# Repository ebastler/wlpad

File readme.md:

# wlpad
wlpad is a simple wireless numpad, designed around a moko MK08A module, and fitting both Hi-Tek 725 as well as MX switches. While the PCB is the same for both switch types, the plate is different.

### Features
* Runs ZMK firmware on a Moko MK08A module - firmware can be found in my [zmk-config](https://github.com/ebastler/zmk-config) repo
* Hi-Tek 725 and Cherry MX compatibility
* Molex Picoblade connectors for battery and plate connection
* Charge indicator LED, some WS2812_2020 and a small 128x32px OLED can be placed on the plate

This PCB was painly made as a proof-of-concept for my Hi-Tek 725 footprints, and to try the MK08A module and MAX17048 fuel gauge chip on an actual PCB. The latter already found its way into my [Osprey](https://github.com/ebastler/osprey). 

rc1.0 had some issues (vertical 2u keys rotated by 180°, LEDs on plate connected to GND instead of VDD), which were addressed by the current rc1.1 version. However, the rc1.1 version has not been (and probably will not be) prototyped - use at your own risk. Please report back if you successfully tested such a PCB.

### Renders (rc1.1)

### Pixtures (rc1.0)

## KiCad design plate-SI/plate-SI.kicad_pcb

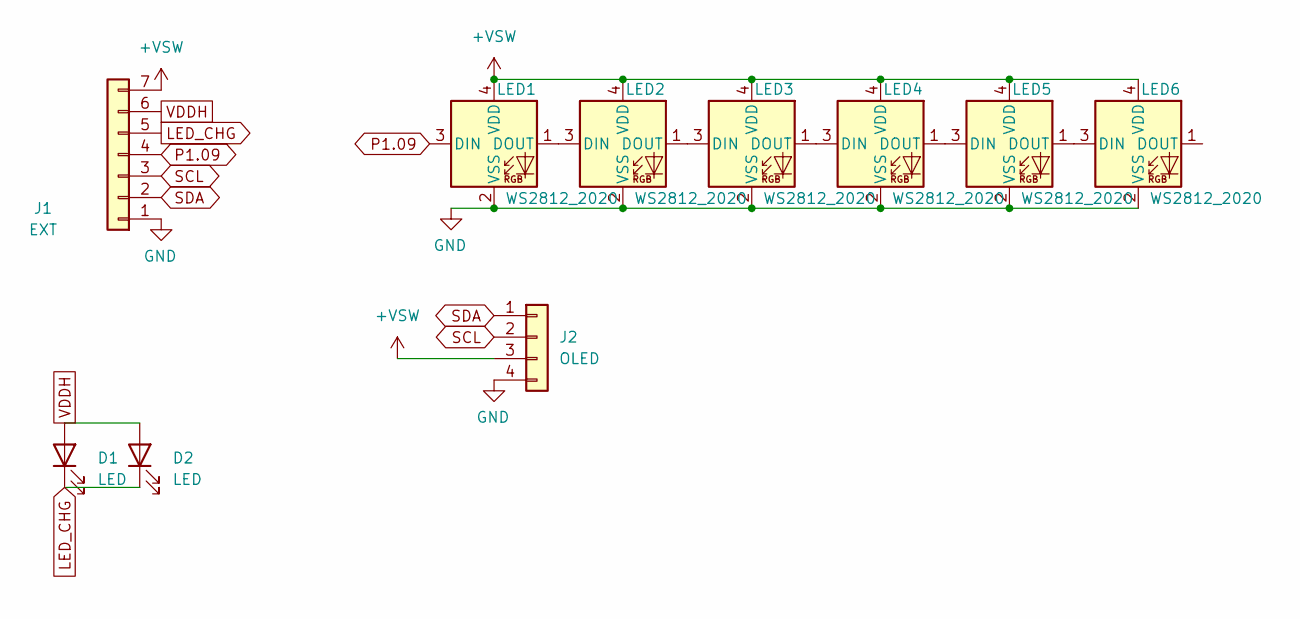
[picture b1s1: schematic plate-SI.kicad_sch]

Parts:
D1: LED; LED_0805_2012Metric_Pad1.15x1.40mm_HandSolder
D2: LED; LED_Rectangular_W3.0mm_H2.0mm
J1: EXT; Molex_PicoBlade_53048-0710_1x07_P1.25mm_Horizontal
J2: OLED; PinHeader_1x04_P2.54mm_Vertical
LED1, LED2, LED3, LED4, LED5, LED6: WS2812_2020; LED_WS2812_2020

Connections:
+VSW: J1.7, J2.3, LED1.4 (VDD), LED2.4 (VDD), LED3.4 (VDD), LED4.4 (VDD), LED5.4 (VDD), LED6.4 (VDD)
GND: J1.1, J2.4, LED1.2 (VSS), LED2.2 (VSS), LED3.2 (VSS), LED4.2 (VSS), LED5.2 (VSS), LED6.2 (VSS)
LED_CHG: D1.1 (K), D2.1 (K), J1.5
unnamed: LED1.1 (DOUT), LED2.3 (DIN)
unnamed: LED2.1 (DOUT), LED3.3 (DIN)
unnamed: LED3.1 (DOUT), LED4.3 (DIN)
unnamed: LED4.1 (DOUT), LED5.3 (DIN)
unnamed: LED5.1 (DOUT), LED6.3 (DIN)
P1.09: J1.4, LED1.3 (DIN)
SCL: J1.3, J2.2
SDA: J1.2, J2.1
VDDH: D1.2 (A), D2.2 (A), J1.6

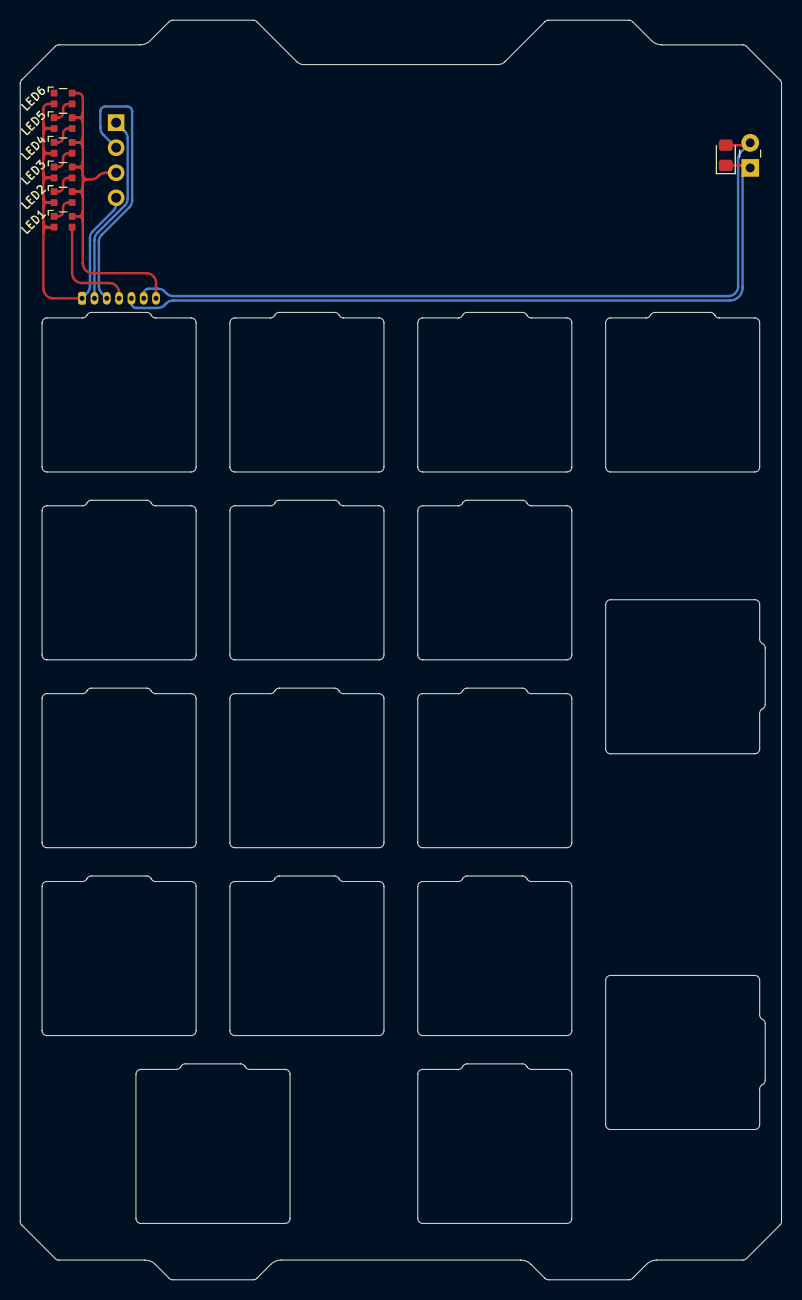
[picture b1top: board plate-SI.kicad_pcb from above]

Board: 2 copper layers, 77.2 x 127.7 mm, 10 parts (1 on the bottom side), 12 nets.

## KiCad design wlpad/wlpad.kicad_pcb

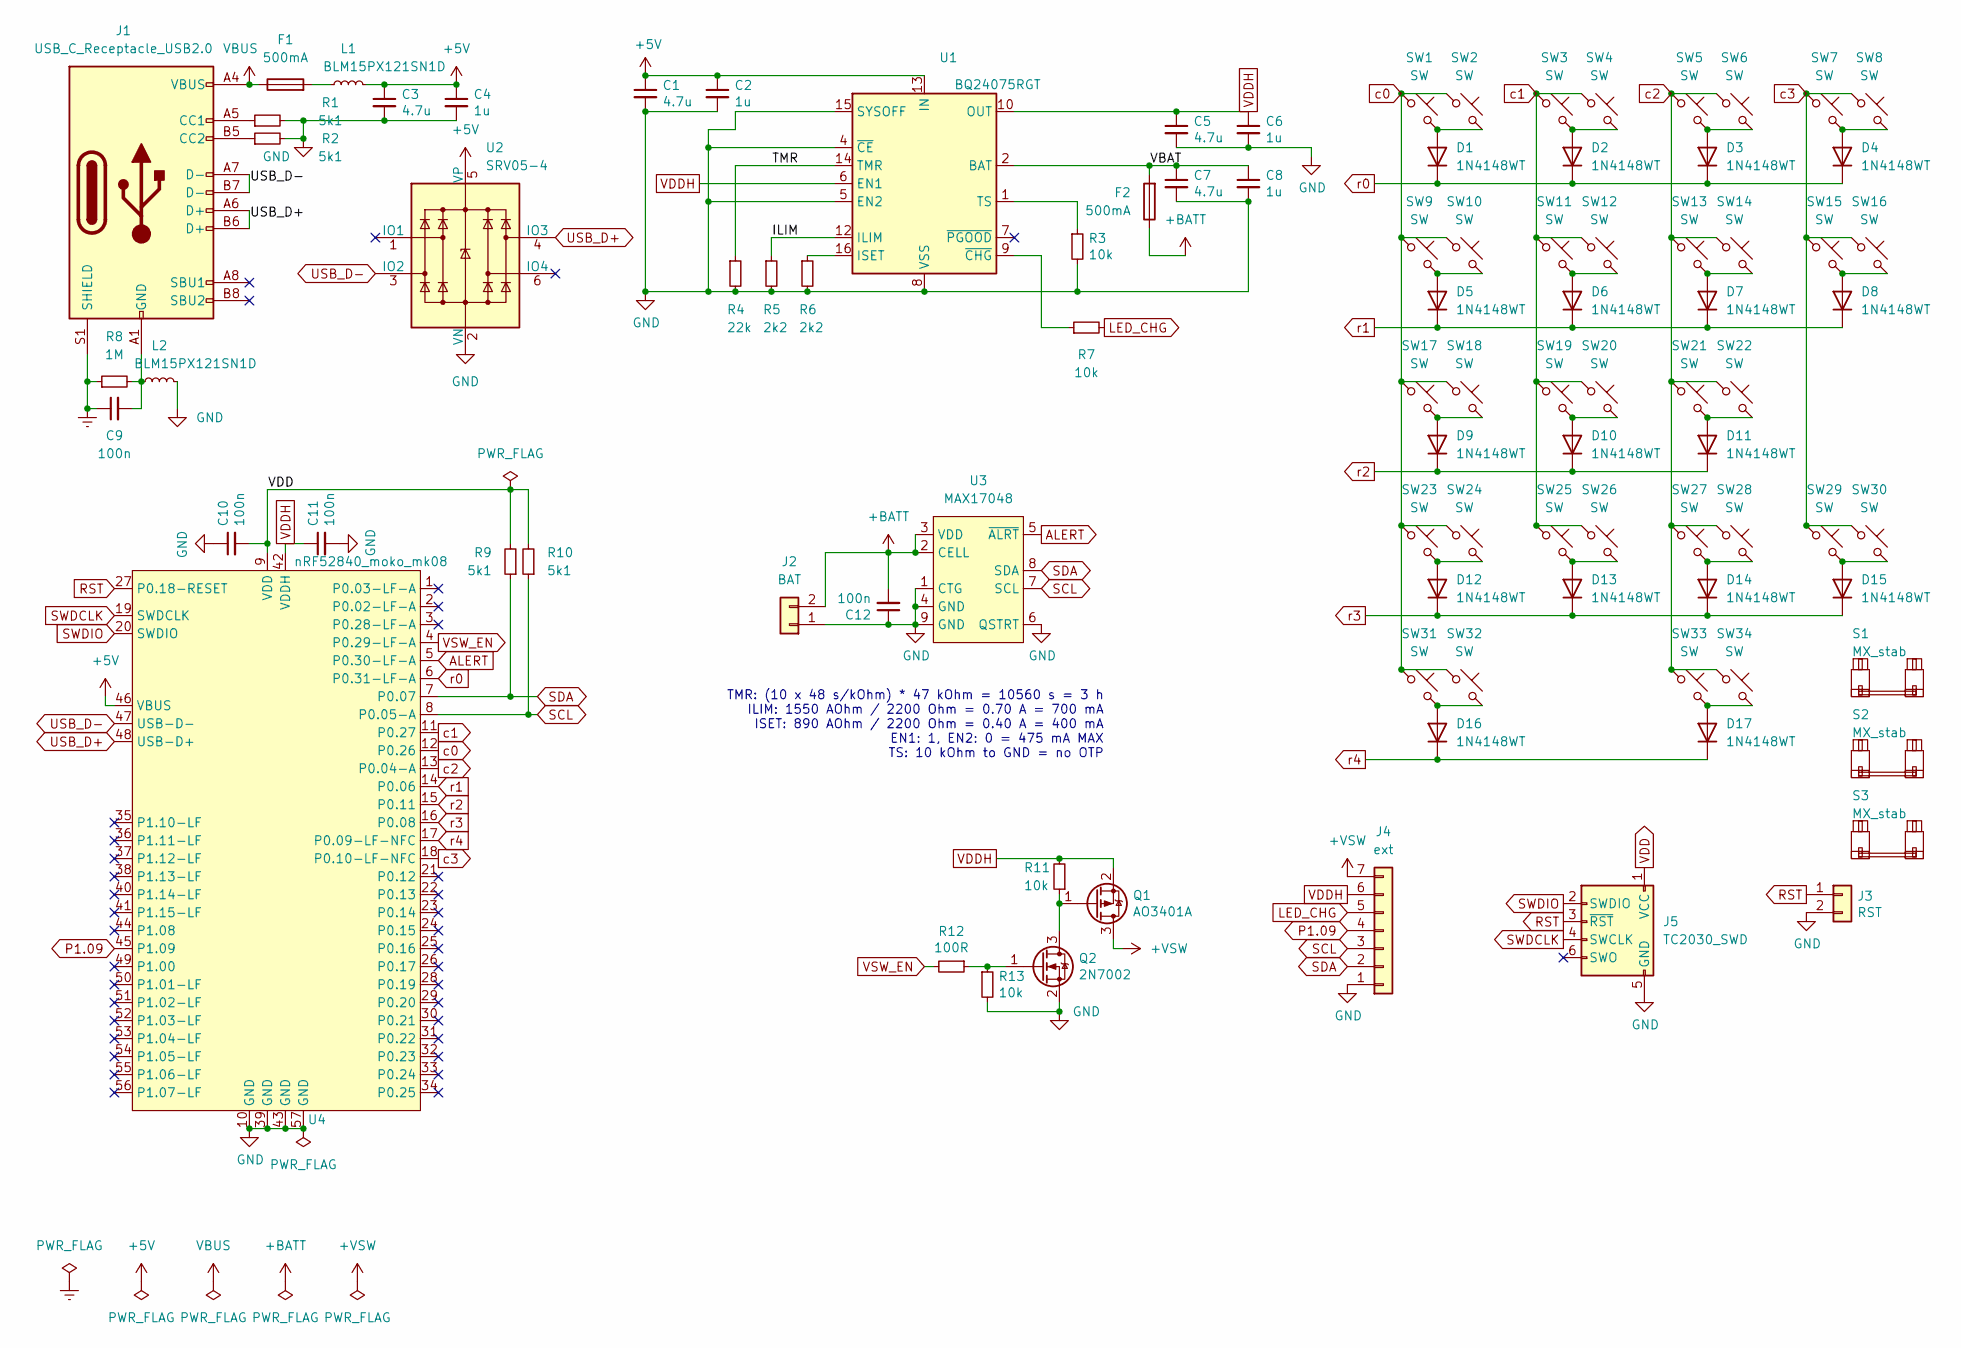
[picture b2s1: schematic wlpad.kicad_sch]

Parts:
C1, C3, C5, C7: 4.7u; C_0402_1005Metric; LCSC C23733
C2, C4, C6, C8: 1u; C_0402_1005Metric; LCSC C52923
C9: 100n; C_0402_1005Metric
C10, C11, C12: 100n; C_0402_1005Metric; LCSC C52923
D1, D2, D3, D4, D5, D6, D7, D8, D9, D10, D11, D12, D13, D14, D15, D16, D17: 1N4148WT; D_SOD-523
F1, F2: 500mA; Fuse_0603_1608Metric
J1: USB_C_Receptacle_USB2.0; USB_C_Receptacle_HRO_TYPE-C-31-M-12
J2: BAT; Molex_PicoBlade_53048-0210_1x02_P1.25mm_Horizontal
J3: RST; PinHeader_1x02_P2.54mm_Vertical
J4: ext; Molex_PicoBlade_53048-0710_1x07_P1.25mm_Horizontal
J5: TC2030_SWD; CON_TC2030_outlined
L1, L2: BLM15PX121SN1D; L_0402_1005Metric; LCSC C88970
Q1: AO3401A; SOT-23
Q2: 2N7002; SOT-23
R1, R2, R9, R10: 5k1; R_0402_1005Metric
R3, R7: 10k; R_0402_1005Metric; LCSC C25744
R4: 22k; R_0402_1005Metric; LCSC C25792
R5: 2k2; R_0402_1005Metric; LCSC C25867
R6: 2k2; R_0402_1005Metric; LCSC C25744
R8: 1M; R_0402_1005Metric
R11, R13: 10k; R_0402_1005Metric
R12: 100R; R_0402_1005Metric
S1, S2, S3: MX_stab; STAB_MX_P_2u
SW1, SW3, SW5, SW7, SW9, SW11, SW13, SW15, SW17, SW19, SW21, SW23, SW25, SW27, SW29, SW31, SW33: SW; SW_HiTek_1u
SW2, SW4, SW6, SW8, SW10, SW12, SW14, SW16, SW18, SW20, SW22, SW24, SW26, SW28, SW30, SW32, SW34: SW; SW_MX_1u
U1: BQ24075RGT; VQFN-16-1EP_3x3mm_P0.5mm_EP1.6x1.6mm
U2: SRV05-4; SOT-23-6
U3: MAX17048; DFN-8-1EP_2x2mm_P0.5mm_EP0.7x1.3mm
U4: nRF52840_moko_mk08; nRF52840_moko_mk08_HS

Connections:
+5V: C1.1, C2.1, C3.1, C4.1, L1.2, U1.13 (IN), U2.5 (VP), U4.46 (VBUS)
+BATT: C12.2, F2.1, J2.2, U3.2 (CELL), U3.3 (VDD)
+VSW: J4.7, Q1.3 (D)
/ILIM: R5.1, U1.12 (ILIM)
/TMR: R4.1, U1.14 (TMR)
/VBAT: C7.1, C8.1, F2.2, U1.2 (BAT), U1.3 (BAT)
ALERT: U3.5 (~ALRT), U4.5 (P0.30-LF-A)
Earth: C9.1, J1.S1 (SHIELD), R8.1
GND: C1.2, C2.2, C3.2, C4.2, C5.2, C6.2, C7.2, C8.2, C10.1, C11.2, C12.1, J2.1, J3.2, J4.1, J5.5 (GND), L2.2, Q2.2 (S), R1.2, R2.2, R3.2, R4.2, R5.2, R6.2, R13.2, U1.4 (~CE), U1.5 (EN2), U1.8 (VSS), U1.15 (SYSOFF), U1.17 (VSS), U2.2 (VN), U3.1 (CTG), U3.4 (GND), U3.6 (QSTRT), U3.9 (GND), U4.10 (GND), U4.39 (GND), U4.43 (GND), U4.57 (GND)
LED_CHG: J4.5, R7.2
unnamed: C9.2, J1.A1 (GND), J1.A12 (GND), J1.B1 (GND), J1.B12 (GND), L2.1, R8.2
unnamed: D1.2 (A), SW1.2, SW2.2
unnamed: D2.2 (A), SW3.2, SW4.2
unnamed: D3.2 (A), SW5.2, SW6.2
unnamed: D4.2 (A), SW7.2, SW8.2
unnamed: D5.2 (A), SW9.2, SW10.2
unnamed: D6.2 (A), SW11.2, SW12.2
unnamed: D7.2 (A), SW13.2, SW14.2
unnamed: D8.2 (A), SW15.2, SW16.2
unnamed: D9.2 (A), SW17.2, SW18.2
unnamed: D10.2 (A), SW19.2, SW20.2
unnamed: D11.2 (A), SW21.2, SW22.2
unnamed: D12.2 (A), SW23.2, SW24.2
unnamed: D13.2 (A), SW25.2, SW26.2
unnamed: D14.2 (A), SW27.2, SW28.2
unnamed: D15.2 (A), SW29.2, SW30.2
unnamed: D16.2 (A), SW31.2, SW32.2
unnamed: D17.2 (A), SW33.2, SW34.2
unnamed: F1.2, L1.1
unnamed: J1.A5 (CC1), R1.1
unnamed: J1.B5 (CC2), R2.1
unnamed: Q1.1 (G), Q2.3 (D), R11.1
unnamed: Q2.1 (G), R12.1, R13.1
unnamed: R6.1, U1.16 (ISET)
unnamed: R3.1, U1.1 (TS)
unnamed: R7.1, U1.9 (~CHG)
P1.09: J4.4, U4.45 (P1.09)
RST: J3.1, J5.3 (~RST), U4.27 (P0.18-RESET)
SCL: J4.3, R10.1, U3.7 (SCL), U4.8 (P0.05-A)
SDA: J4.2, R9.1, U3.8 (SDA), U4.7 (P0.07)
SWDCLK: J5.4 (SWCLK), U4.19 (SWDCLK)
SWDIO: J5.2 (SWDIO), U4.20 (SWDIO)
USB_D+: J1.A6 (D+), J1.B6 (D+), U2.4 (IO3), U4.48 (USB-D+)
USB_D-: J1.A7 (D-), J1.B7 (D-), U2.3 (IO2), U4.47 (USB-D-)
VBUS: F1.1, J1.A4 (VBUS), J1.A9 (VBUS), J1.B4 (VBUS), J1.B9 (VBUS)
VDD: C10.2, J5.1 (VCC), R9.2, R10.2, U4.9 (VDD)
VDDH: C5.1, C6.1, C11.1, J4.6, Q1.2 (S), R11.2, U1.6 (EN1), U1.10 (OUT), U1.11 (OUT), U4.42 (VDDH)
VSW_EN: R12.2, U4.4 (P0.29-LF-A)
c0: SW1.1, SW2.1, SW9.1, SW10.1, SW17.1, SW18.1, SW23.1, SW24.1, SW31.1, SW32.1, U4.12 (P0.26)
c1: SW3.1, SW4.1, SW11.1, SW12.1, SW19.1, SW20.1, SW25.1, SW26.1, U4.11 (P0.27)
c2: SW5.1, SW6.1, SW13.1, SW14.1, SW21.1, SW22.1, SW27.1, SW28.1, SW33.1, SW34.1, U4.13 (P0.04-A)
c3: SW7.1, SW8.1, SW15.1, SW16.1, SW29.1, SW30.1, U4.18 (P0.10-LF-NFC)
r0: D1.1 (K), D2.1 (K), D3.1 (K), D4.1 (K), U4.6 (P0.31-LF-A)
r1: D5.1 (K), D6.1 (K), D7.1 (K), D8.1 (K), U4.14 (P0.06)
r2: D9.1 (K), D10.1 (K), D11.1 (K), U4.15 (P0.11)
r3: D12.1 (K), D13.1 (K), D14.1 (K), D15.1 (K), U4.16 (P0.08)
r4: D16.1 (K), D17.1 (K), U4.17 (P0.09-LF-NFC)

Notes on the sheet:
TMR: (10 x 48 s/kOhm) * 47 kOhm = 10560 s = 3 h ILIM: 1550 AOhm / 2200 Ohm = 0.70 A = 700 mA ISET: 890 AOhm / 2200 Ohm = 0.40 A = 400 mA EN1: 1, EN2: 0 = 475 mA MAX TS: 10 kOhm to GND = no OTP

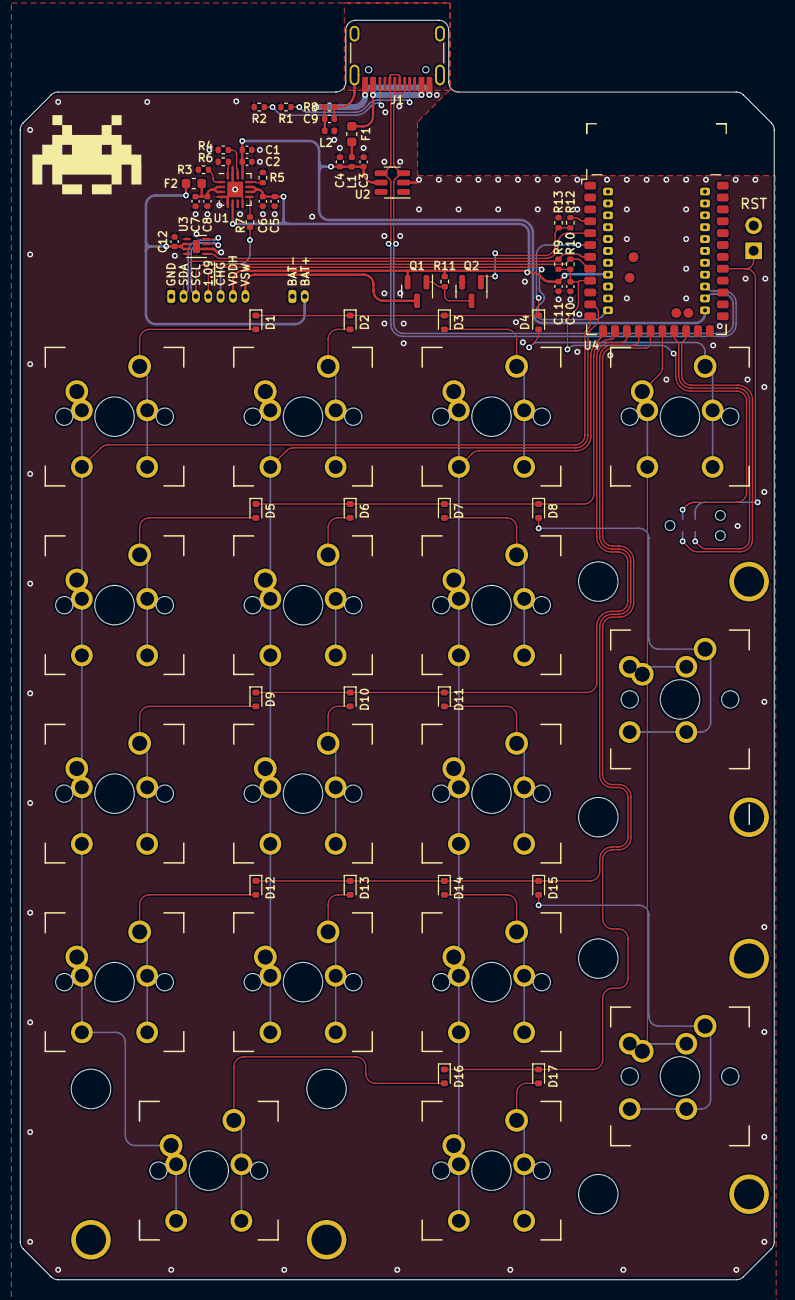
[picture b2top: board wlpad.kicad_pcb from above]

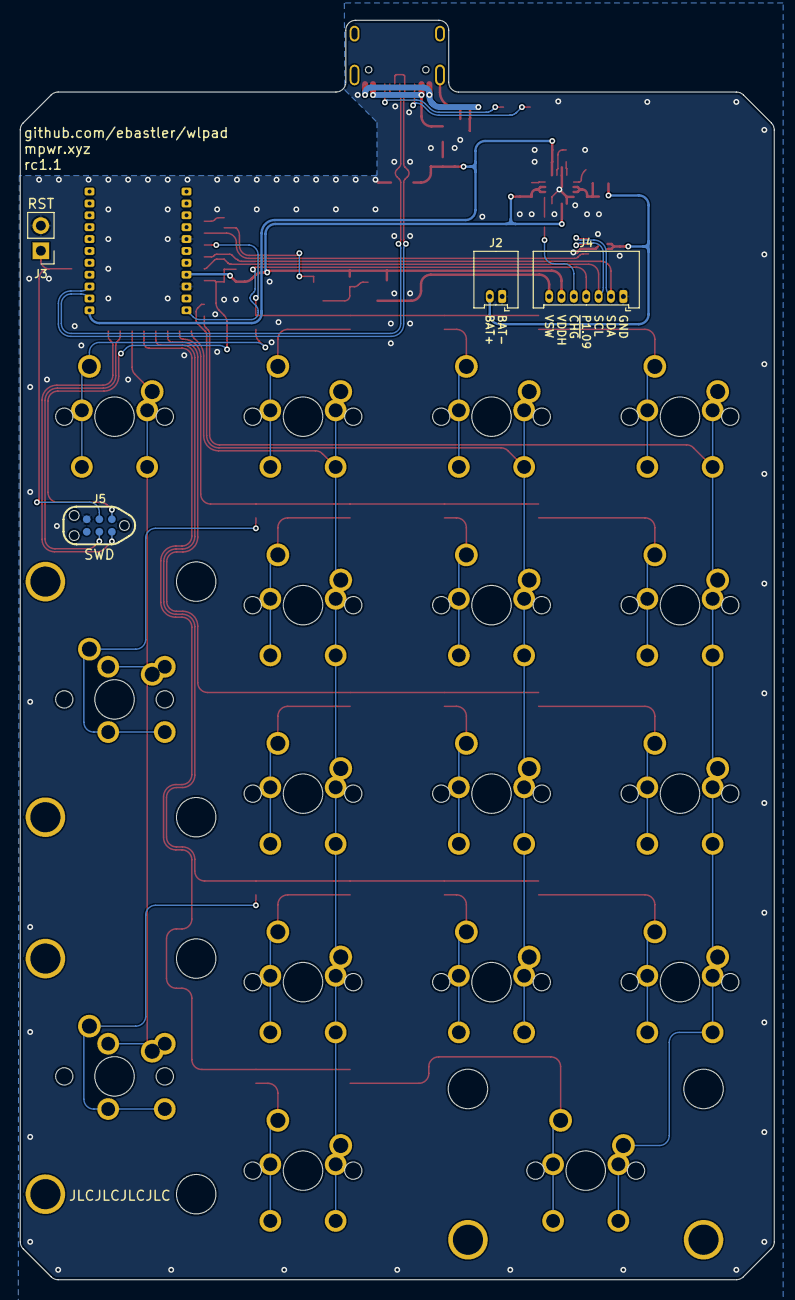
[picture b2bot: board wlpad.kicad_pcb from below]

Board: 2 copper layers, 76.2 x 127.3 mm, 94 parts (4 on the bottom side), 57 nets.

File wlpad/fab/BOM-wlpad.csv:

Comment,Designator,Footprint,LCSC
AO3401A,Q1,SOT-23,C15127
USB_C_Receptacle_USB2.0,J1,USB_C_Receptacle_HRO_TYPE-C-31-M-12,C165948
500mA,"F1,F2",Fuse_0603_1608Metric,C210357
4.7u,"C1,C3,C5,C7",C_0402_1005Metric,C23733
100R,R12,R_0402_1005Metric,C25076
10k,"R11,R13,R3,R6,R7",R_0402_1005Metric,C25744
22k,R4,R_0402_1005Metric,C25792
2k2,R5,R_0402_1005Metric,C25867
5k1,"R1,R10,R2,R9",R_0402_1005Metric,C25905
1M,R8,R_0402_1005Metric,C26083
MAX17048,U3,DFN-8-1EP_2x2mm_P0.5mm_EP0.7x1.3mm,C2682616
BQ24075RGT,U1,VQFN-16-1EP_3x3mm_P0.5mm_EP1.6x1.6mm,C2865459
1N4148WT,"D1,D10,D11,D12,D13,D14,D15,D16,D17,D2,D3,D4,D5,D6,D7,D8,D9",D_SOD-523,C511874
100n,"C10,C11,C12,C2,C4,C6,C8,C9",C_0402_1005Metric,C52923
SRV05-4,U2,SOT-23-6,C558418
2N7002,Q2,SOT-23,C8545
BLM15PX121SN1D,"L1,L2",L_0402_1005Metric,C88970
ext,J4,Molex_PicoBlade_53048-0710_1x07_P1.25mm_Horizontal,
BAT,J2,Molex_PicoBlade_53048-0210_1x02_P1.25mm_Horizontal,

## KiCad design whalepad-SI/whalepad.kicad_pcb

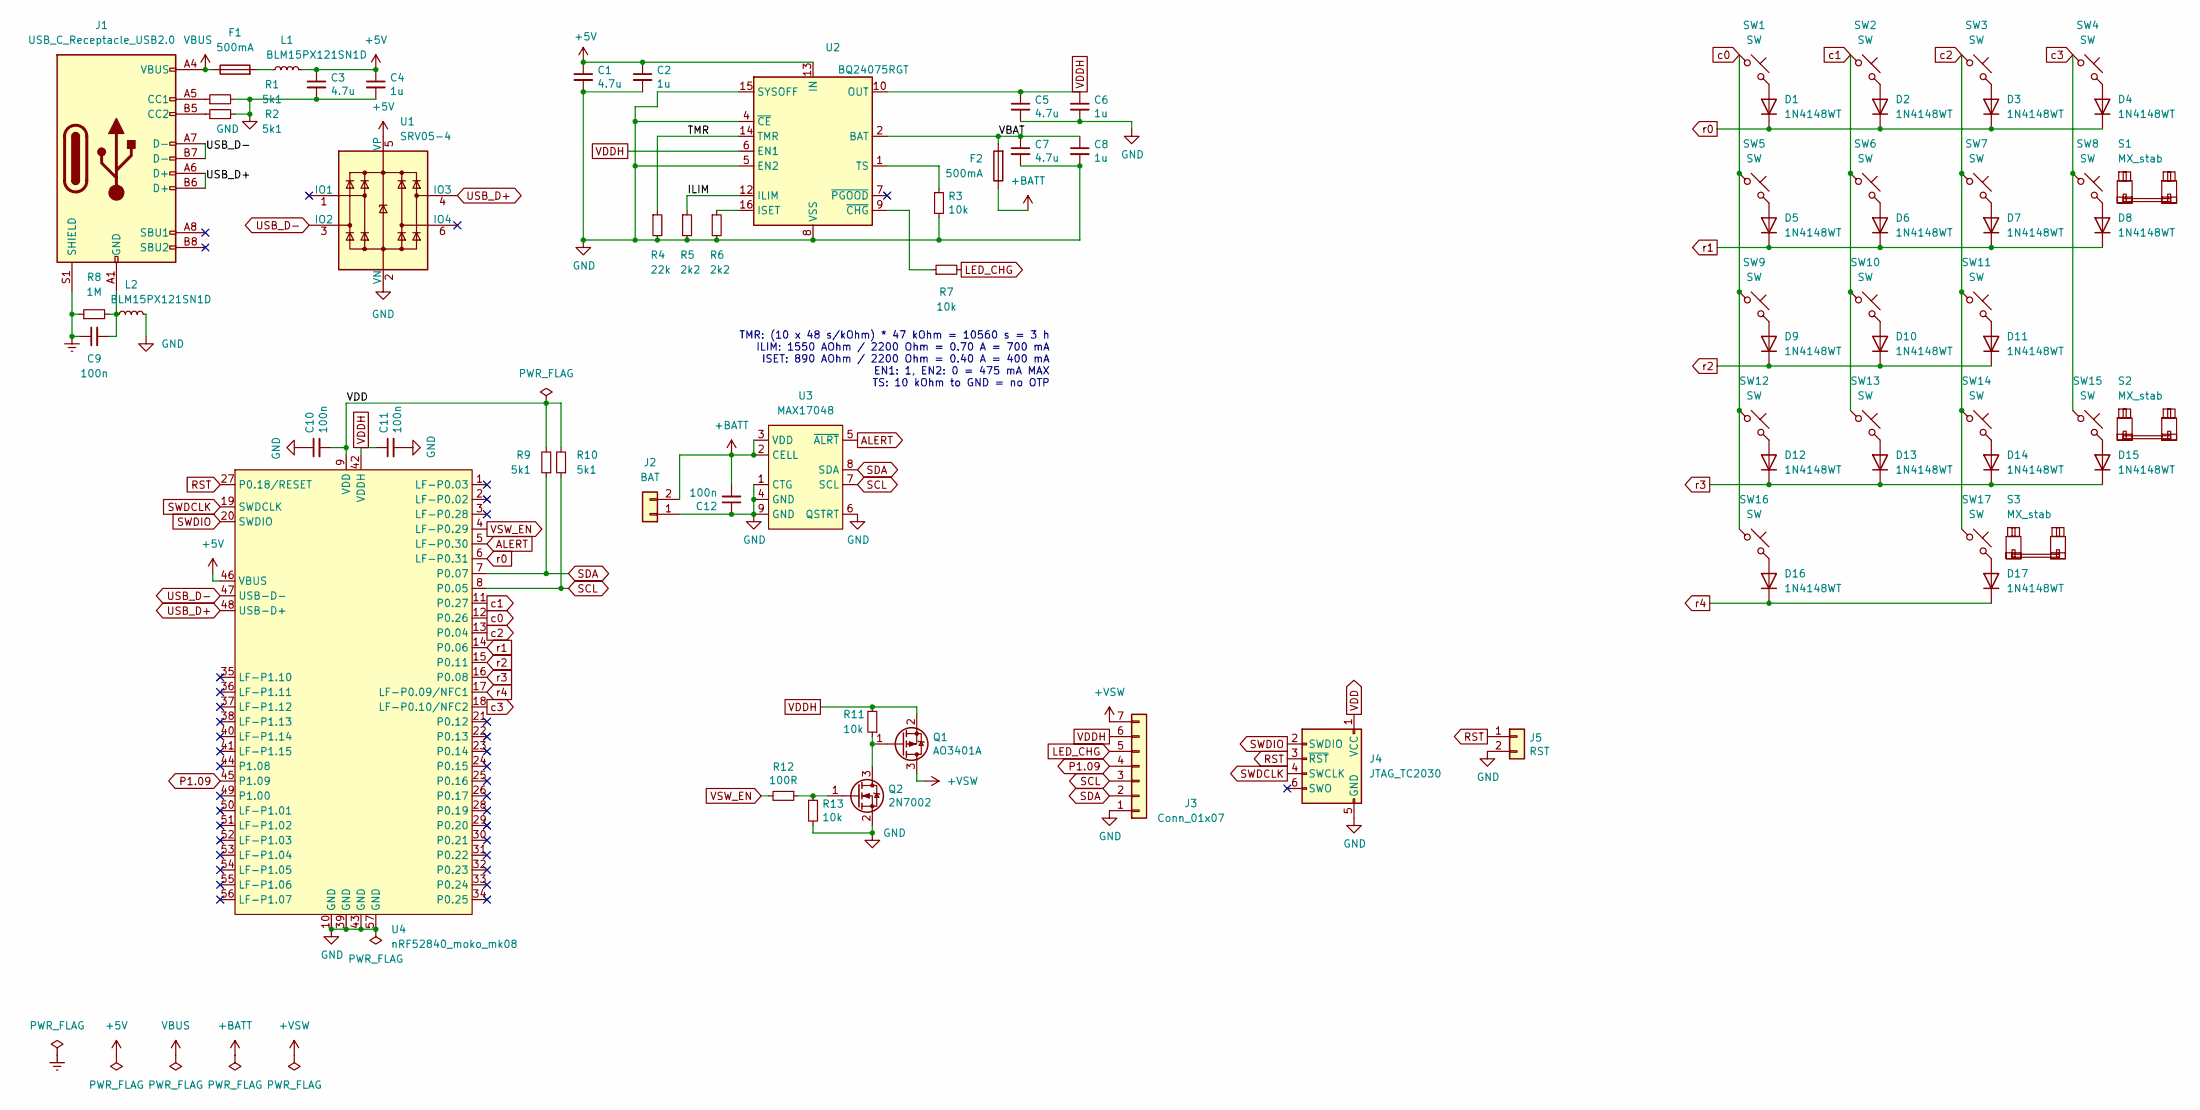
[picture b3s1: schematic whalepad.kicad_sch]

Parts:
C1, C3, C5, C7: 4.7u; C_0402_1005Metric; LCSC C23733
C2, C4, C6, C8: 1u; C_0402_1005Metric; LCSC C52923
C9: 100n; C_0402_1005Metric
C10, C11, C12: 100n; C_0402_1005Metric; LCSC C52923
D1, D2, D3, D4, D5, D6, D7, D8, D9, D10, D11, D12, D13, D14, D15, D16, D17: 1N4148WT; D_SOD-523
F1, F2: 500mA; Fuse_0603_1608Metric
J1: USB_C_Receptacle_USB2.0; USB_C_Receptacle_HRO_TYPE-C-31-M-12
J2: BAT; Molex_PicoBlade_53048-0210_1x02_P1.25mm_Horizontal
J3: Conn_01x07; Molex_PicoBlade_53048-0710_1x07_P1.25mm_Horizontal
J4: JTAG_TC2030; CON_TC2030_outlined
J5: RST; PinHeader_1x02_P2.54mm_Vertical
L1, L2: BLM15PX121SN1D; L_0402_1005Metric; LCSC C88970
Q1: AO3401A; SOT-23
Q2: 2N7002; SOT-23
R1, R2, R9, R10: 5k1; R_0402_1005Metric
R3, R7: 10k; R_0402_1005Metric; LCSC C25744
R4: 22k; R_0402_1005Metric; LCSC C25792
R5: 2k2; R_0402_1005Metric; LCSC C25867
R6: 2k2; R_0402_1005Metric; LCSC C25744
R8: 1M; R_0402_1005Metric
R11, R13: 10k; R_0402_1005Metric
R12: 100R; R_0402_1005Metric
S1, S2, S3: MX_stab; STAB_MX_P_2u
SW1, SW2, SW3, SW4, SW5, SW6, SW7, SW8, SW9, SW10, SW11, SW12, SW13, SW14, SW15, SW16, SW17: SW; SW_HiTek_MX_1u
U1: SRV05-4; SOT-23-6
U2: BQ24075RGT; VQFN-16-1EP_3x3mm_P0.5mm_EP1.6x1.6mm
U3: MAX17048; DFN-8-1EP_2x2mm_P0.5mm_EP0.7x1.3mm
U4: nRF52840_moko_mk08

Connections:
+5V: C1.1, C2.1, C3.1, C4.1, L1.2, U1.5 (VP), U2.13 (IN), U4.46 (VBUS)
+BATT: C12.2, F2.1, J2.2, U3.2 (CELL), U3.3 (VDD)
+VSW: J3.7, Q1.3 (D)
/ILIM: R5.1, U2.12 (ILIM)
/TMR: R4.1, U2.14 (TMR)
/VBAT: C7.1, C8.1, F2.2, U2.2 (BAT), U2.3 (BAT)
ALERT: U3.5 (~ALRT), U4.5 (LF-P0.30)
Earth: C9.1, J1.S1 (SHIELD), R8.1
GND: C1.2, C2.2, C3.2, C4.2, C5.2, C6.2, C7.2, C8.2, C10.1, C11.2, C12.1, J2.1, J3.1, J4.5 (GND), J5.2, L2.2, Q2.2 (S), R1.2, R2.2, R3.2, R4.2, R5.2, R6.2, R13.2, U1.2 (VN), U2.4 (~CE), U2.5 (EN2), U2.8 (VSS), U2.15 (SYSOFF), U2.17 (VSS), U3.1 (CTG), U3.4 (GND), U3.6 (QSTRT), U3.9 (GND), U4.10 (GND), U4.39 (GND), U4.43 (GND), U4.57 (GND)
LED_CHG: J3.5, R7.2
unnamed: C9.2, J1.A1 (GND), J1.A12 (GND), J1.B1 (GND), J1.B12 (GND), L2.1, R8.2
unnamed: D1.2 (A), SW1.2
unnamed: D2.2 (A), SW2.2
unnamed: D3.2 (A), SW3.2
unnamed: D4.2 (A), SW4.2
unnamed: D5.2 (A), SW5.2
unnamed: D6.2 (A), SW6.2
unnamed: D7.2 (A), SW7.2
unnamed: D8.2 (A), SW8.2
unnamed: D9.2 (A), SW9.2
unnamed: D10.2 (A), SW10.2
unnamed: D11.2 (A), SW11.2
unnamed: D12.2 (A), SW12.2
unnamed: D13.2 (A), SW13.2
unnamed: D14.2 (A), SW14.2
unnamed: D15.2 (A), SW15.2
unnamed: D16.2 (A), SW16.2
unnamed: D17.2 (A), SW17.2
unnamed: F1.2, L1.1
unnamed: J1.A5 (CC1), R1.1
unnamed: J1.B5 (CC2), R2.1
unnamed: Q1.1 (G), Q2.3 (D), R11.1
unnamed: Q2.1 (G), R12.1, R13.1
unnamed: R3.1, U2.1 (TS)
unnamed: R6.1, U2.16 (ISET)
unnamed: R7.1, U2.9 (~CHG)
P1.09: J3.4, U4.45 (P1.09)
RST: J4.3 (~RST), J5.1, U4.27 (P0.18/RESET)
SCL: J3.3, R10.1, U3.7 (SCL), U4.8 (P0.05)
SDA: J3.2, R9.1, U3.8 (SDA), U4.7 (P0.07)
SWDCLK: J4.4 (SWCLK), U4.19 (SWDCLK)
SWDIO: J4.2 (SWDIO), U4.20 (SWDIO)
USB_D+: J1.A6 (D+), J1.B6 (D+), U1.4 (IO3), U4.48 (USB-D+)
USB_D-: J1.A7 (D-), J1.B7 (D-), U1.3 (IO2), U4.47 (USB-D-)
VBUS: F1.1, J1.A4 (VBUS), J1.A9 (VBUS), J1.B4 (VBUS), J1.B9 (VBUS)
VDD: C10.2, J4.1 (VCC), R9.2, R10.2, U4.9 (VDD)
VDDH: C5.1, C6.1, C11.1, J3.6, Q1.2 (S), R11.2, U2.6 (EN1), U2.10 (OUT), U2.11 (OUT), U4.42 (VDDH)
VSW_EN: R12.2, U4.4 (LF-P0.29)
c0: SW1.1, SW5.1, SW9.1, SW12.1, SW16.1, U4.12 (P0.26)
c1: SW2.1, SW6.1, SW10.1, SW13.1, U4.11 (P0.27)
c2: SW3.1, SW7.1, SW11.1, SW14.1, SW17.1, U4.13 (P0.04)
c3: SW4.1, SW8.1, SW15.1, U4.18 (LF-P0.10/NFC2)
r0: D1.1 (K), D2.1 (K), D3.1 (K), D4.1 (K), U4.6 (LF-P0.31)
r1: D5.1 (K), D6.1 (K), D7.1 (K), D8.1 (K), U4.14 (P0.06)
r2: D9.1 (K), D10.1 (K), D11.1 (K), U4.15 (P0.11)
r3: D12.1 (K), D13.1 (K), D14.1 (K), D15.1 (K), U4.16 (P0.08)
r4: D16.1 (K), D17.1 (K), U4.17 (LF-P0.09/NFC1)

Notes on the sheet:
TMR: (10 x 48 s/kOhm) * 47 kOhm = 10560 s = 3 h ILIM: 1550 AOhm / 2200 Ohm = 0.70 A = 700 mA ISET: 890 AOhm / 2200 Ohm = 0.40 A = 400 mA EN1: 1, EN2: 0 = 475 mA MAX TS: 10 kOhm to GND = no OTP

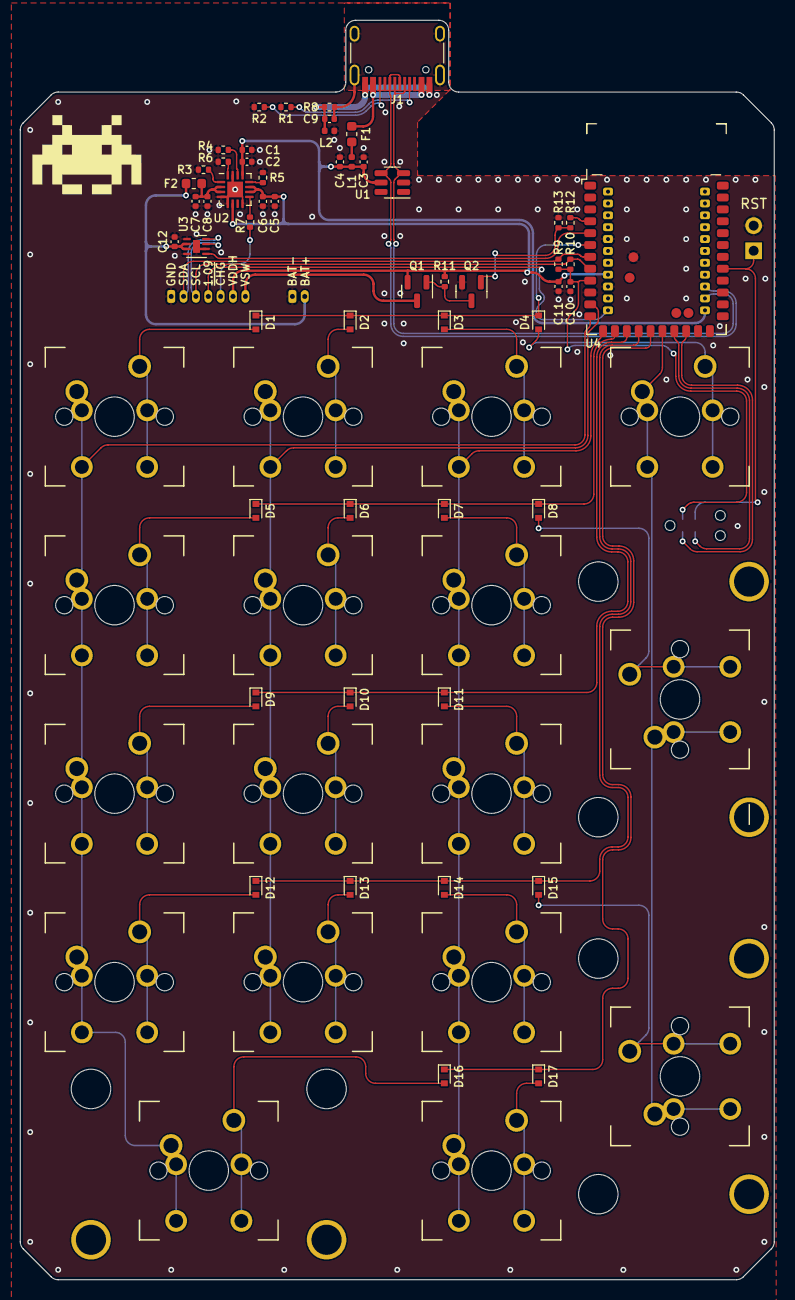
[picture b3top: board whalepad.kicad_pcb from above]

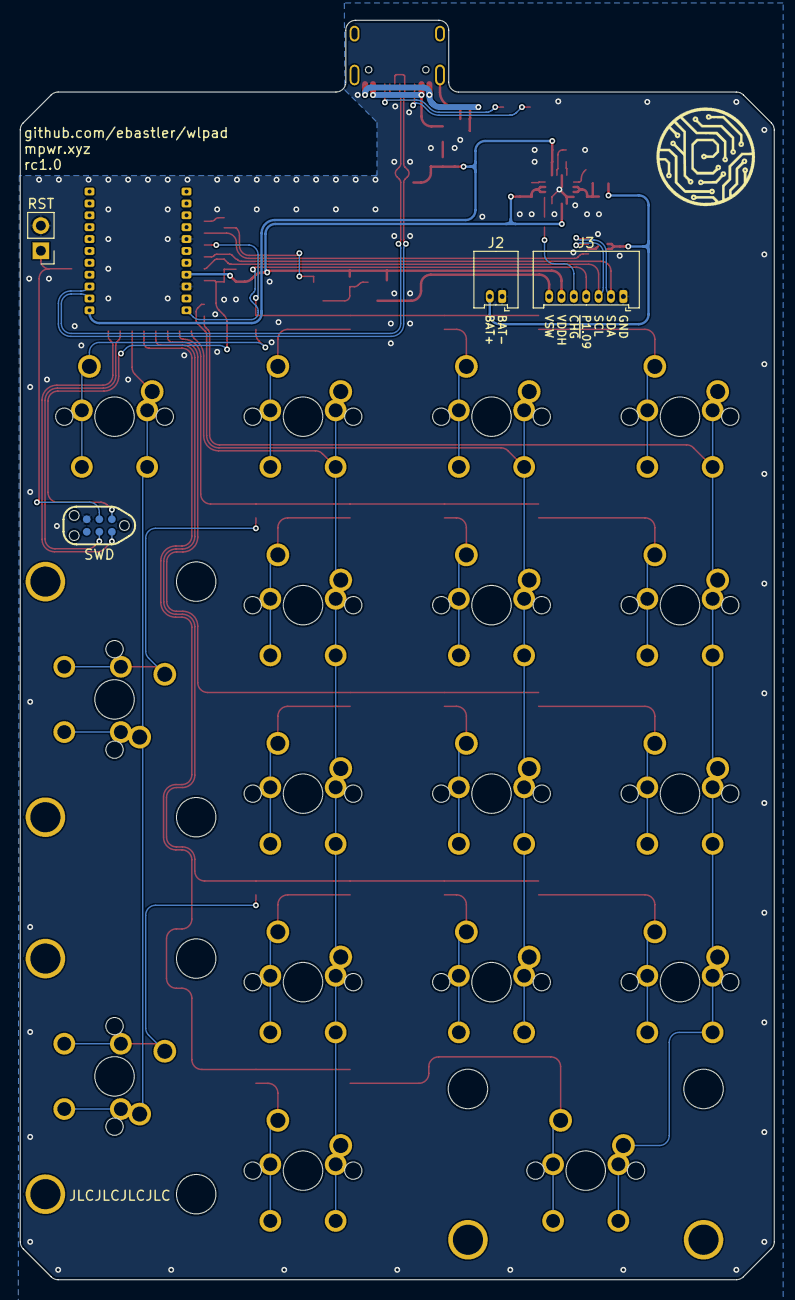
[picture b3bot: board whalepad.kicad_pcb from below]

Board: 2 copper layers, 76.2 x 127.3 mm, 77 parts (4 on the bottom side), 57 nets.

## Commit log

2022-07-14 first proto rev
2022-07-14 added license
2023-12-25 changed gitignore so it would not delete .csv files
2023-12-25 renamed license to be inline with my other newer repos
2023-12-25 fixed wrong orientation of vertical 2u keys, renamed project folder, switched to PCM marbastlib
2023-12-25 updated .step
2023-12-25 fixed SI plate, added MX plate
2023-12-25 added readme
2023-12-25 fixed URLs in readme
